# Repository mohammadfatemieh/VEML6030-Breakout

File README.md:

# VEML6030-Breakout
Breakout with Vishay VEML6030 Light Sensor.

* Open-Source and released under the [Creative Commons Attribution Share-Alike License](https://creativecommons.org/licenses/by-sa/4.0/).
* **[Documentation on learn.watterott.com](https://learn.watterott.com)**

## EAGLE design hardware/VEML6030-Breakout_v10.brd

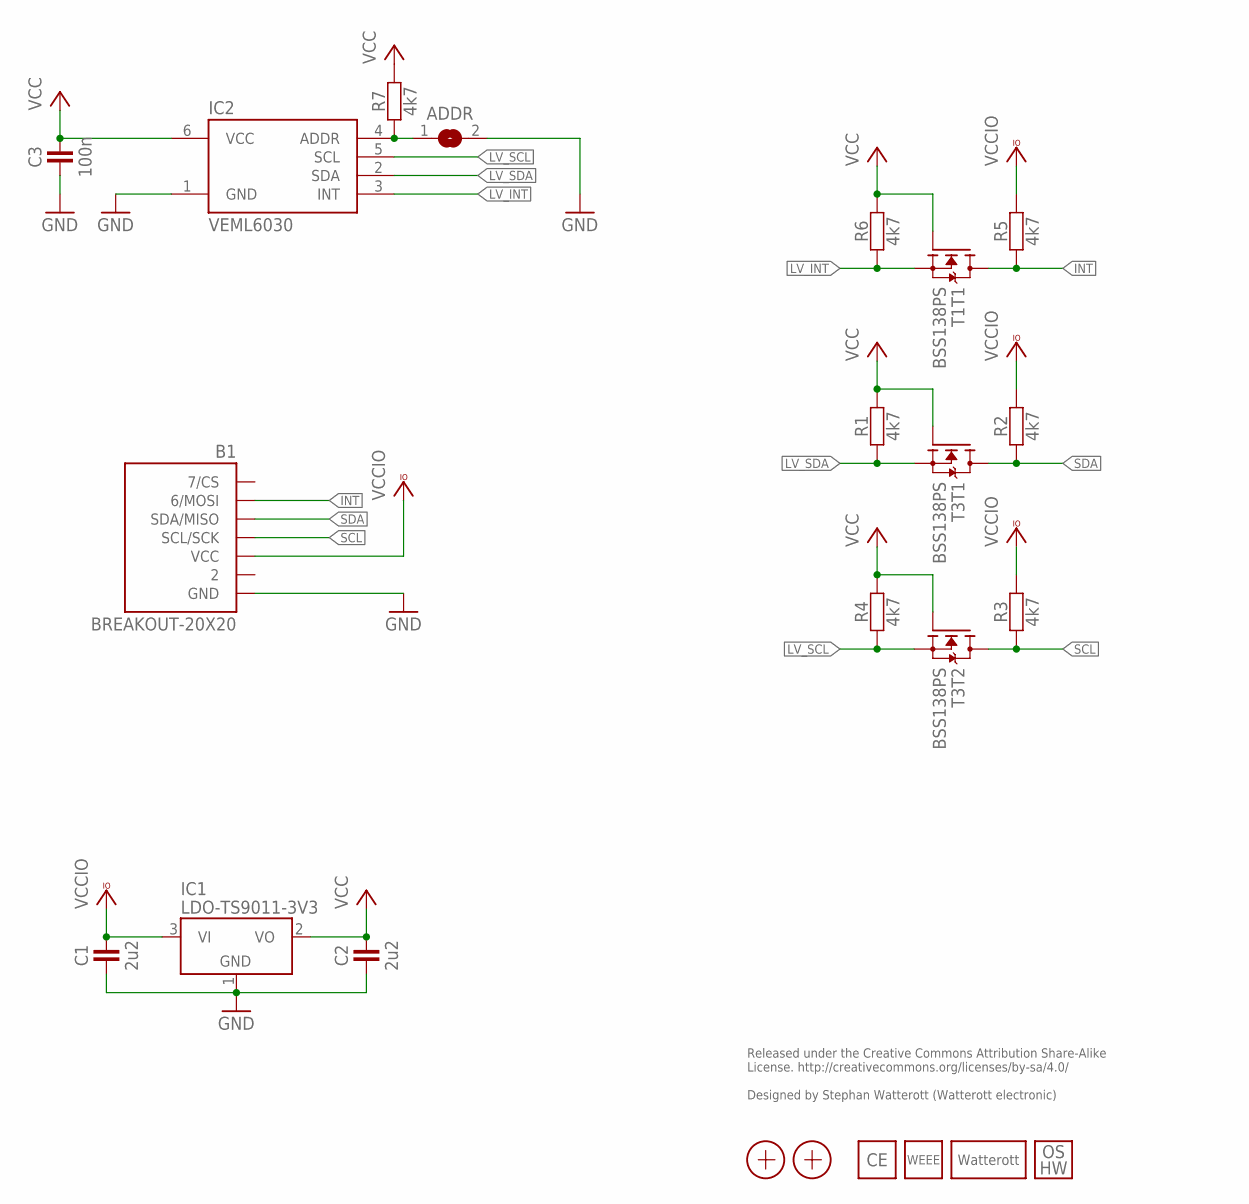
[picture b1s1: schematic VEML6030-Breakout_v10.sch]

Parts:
ADDR: JUMPER2-0603-NC; JUMPER2-0603_NC
B1: BREAKOUT-20X20
C1, C2: 2u2; C0402
C3: 100n; C0402
IC1: LDO-TS9011-3V3; SOT23
IC2: VEML6030
LOGO3: LOGO_WEEE-4; WEEE_4MM
LOGO4: LOGO_CE-4; CE_4MM
LOGO5: LOGO_SPARK-4; SPARK_4MM
LOGO6: LOGO_OSHW-2; OSHW_2MM
R1, R2, R3, R4, R5, R6, R7: 4k7; C0402
T1, T3: BSS138PS; SOT363
X1, X2: PASSER-07; PASSER_07MM

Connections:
GND: ADDR.2, B1.GND, C1.1, C2.1, C3.1, IC1.1 (GND), IC2.1 (GND)
INT: B1.MOSI (6/MOSI), R5.1, T1.6 (D)
LV_INT: IC2.3 (INT), R6.1, T1.1 (S)
LV_SCL: IC2.5 (SCL), R4.1, T3.4 (S)
LV_SDA: IC2.2 (SDA), R1.1, T3.1 (S)
unnamed: ADDR.1, IC2.4 (ADDR), R7.1
SCL: B1.SCL/SCK, R3.1, T3.3 (D)
SDA: B1.SDA/MISO, R2.1, T3.6 (D)
VCC: C2.2, C3.2, IC1.2 (VO), IC2.6 (VCC), R1.2, R4.2, R6.2, R7.2, T1.2 (G), T3.2 (G), T3.5 (G)
VCCIO: B1.VCC, C1.2, IC1.3 (VI), R2.2, R3.2, R5.2

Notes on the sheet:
Released under the Creative Commons Attribution Share-Alike License. http://creativecommons.org/licenses/by-sa/4.0/ Designed by Stephan Watterott (Watterott electronic)

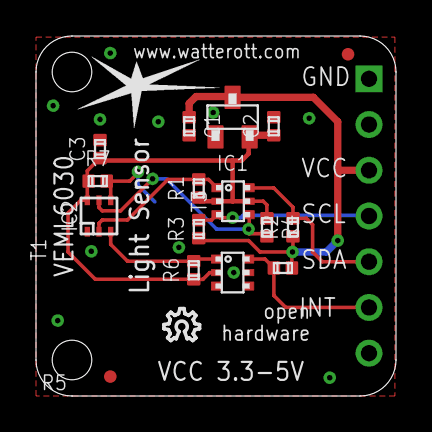
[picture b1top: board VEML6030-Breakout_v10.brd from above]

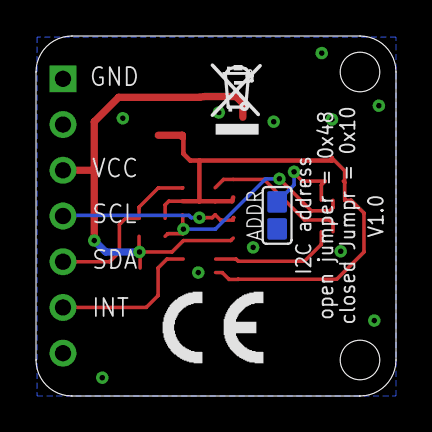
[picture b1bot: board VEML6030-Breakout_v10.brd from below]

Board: 2 copper layers, 20.0 x 20.0 mm, 22 parts (3 on the bottom side), 10 nets.

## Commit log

2019-02-02 added readme
2019-11-03 added schematics and layout
